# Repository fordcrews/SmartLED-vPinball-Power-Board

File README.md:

# SmartLED & Pinball Power Board v1

## Overview
SmartLED v1 is a modular, ATX-powered breakout board designed for ESP32-based lighting, solenoid, and accessory control projects such as:

- Virtual Pinball Machines  
- Holiday Light Shows  
- Aquarium Automation  
- Home Decor Lighting Systems

## Features

### 🔌 ATX/Mini-ITX Power Supply Input
- Standard 24-pin ATX connector
- `PS_ON#` control via MOSFET (GPIO or jumper selectable)
- Uses `+5VSB` to power ESP32 independently of main rails

### 🧠 ESP32 DevKitC Integration
- Supports 30-pin DevKitC boards
- Powered by +5VSB with onboard regulation
- Breakout header for unused GPIOs

### 💡 Buffered LED Outputs (8x)
- 3-pin JST outputs with:
  - AHCT125 level shifters (3.3V to 5V)
  - Selectable 5V or 12V via jumper
  - Fused output per channel

### 🧰 Dual Terminal Access
- Breadboard header (J10) and cabinet terminal block (J11)
- Shared pinout, use either or both

### 🧩 GPIO Expansion
- I²C header (GND, VCC, SDA, SCL)
- Additional GPIOs for sensors, encoders, buttons, etc.

### 🔋 MOSFET Driver Sockets
- 2–4 TO-220 MOSFET slots (e.g. IRLZ44N)
- Gate control via GPIO or jumper
- Voltage selectable (5V/12V AUX)
- For solenoids, fans, relays, motors, etc.

### 🔌 Power Outputs
- USB-C / Micro USB 5V **outputs**
- 5V/12V Barrel jack **outputs**
- Drive external Pi, LED drivers, amps, etc.

### ⚡ Cabinet Power Switch Output
- Optional switched line to control cabinet-wide power
- Triggered via ESP32 or logic jumper

## Optional / Phase 2 Ideas
- Break-off compact section
- Raspberry Pi header (Zero/Full support)
- OLED display pinout for power/usage stats
- Software-based PSU shutdown/watchdog

## Design Goals
- One ATX cable powers your entire rig
- Clean, modular, safe wiring
- Minimalist or advanced builds supported
- Great for compact lighting builds or full-featured pinball control systems

---

📁 PCB, schematic, BOM, and KiCad project files coming soon!

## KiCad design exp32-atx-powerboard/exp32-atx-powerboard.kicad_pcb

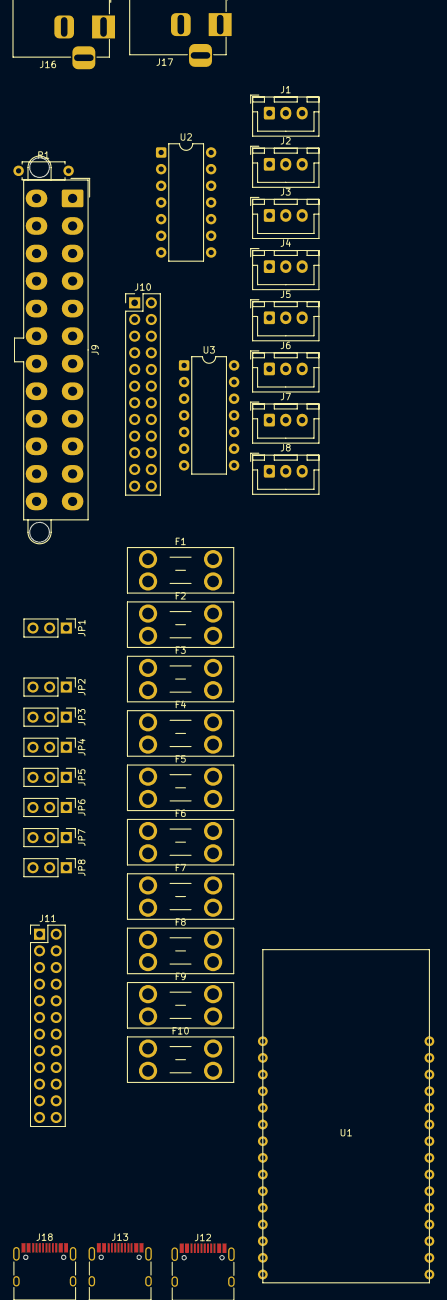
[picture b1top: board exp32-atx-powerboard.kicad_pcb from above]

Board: 2 copper layers, 38 parts (0 on the bottom side), 40 nets, no tracks yet.

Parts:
F1, F2, F3, F4, F5, F6, F7, F8, F9, F10: Fuse; Fuseholder_Blade_Mini_Keystone_3568
J1, J2, J3, J4, J5, J6, J7, J8: Conn_01x03; JST_XH_B3B-XH-A_1x03_P2.50mm_Vertical
J9: Conn_02x12_Top_Bottom; Molex_Mini-Fit_Jr_5566-24A2_2x12_P4.20mm_Vertical
J10, J11: Conn_02x12_Top_Bottom; PinHeader_2x12_P2.54mm_Vertical
J12, J13, J18: USB_C_Receptacle_PowerOnly_6P; USB_C_Receptacle_HRO_TYPE-C-31-M-12
J16, J17: Conn_01x02; BarrelJack_Horizontal
JP1, JP2, JP3, JP4, JP5, JP6, JP7, JP8: Jumper_3_Open; PinHeader_1x03_P2.54mm_Vertical
R1: 10k; R_Axial_DIN0207_L6.3mm_D2.5mm_P7.62mm_Horizontal
U1: ESP32-WROOM-32; ESP32-DevKitC_30Pin
U2, U3: 74AHCT125; DIP-14_W7.62mm

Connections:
+3.3V: J9.1, J10.1, J10.2, J10.3, J11.1, J11.2, J11.3
+5VAUX: F10.2, J10.4, J10.5, J10.6, J10.7, J10.8, J10.9, J11.4, J11.5, J11.6, J11.7, J11.8, J11.9, J12.A9 (VBUS), J12.B9 (VBUS), J18.A9 (VBUS), J18.B9 (VBUS)
+5VLED: J9.20, JP1.1 (A), JP2.1 (A), JP3.1 (A), JP4.1 (A), JP5.1 (A), JP6.1 (A), JP7.1 (A), JP8.1 (A)
+5VLOGIC: U2.14 (VCC), U3.14 (VCC)
+5V_LOGIC: J9.9, R1.1
+12VAUX: F9.1, J10.10, J10.11, J10.12, J11.10, J11.11, J11.12, J16.2, J17.2
+12VLED: J9.11, JP2.3 (B), JP3.3 (B), JP4.3 (B), JP5.3 (B), JP6.3 (B), JP7.3 (B), JP8.3 (B)
/DATA1_IN: U1.27 (IO16), U2.2
/DATA2_IN: U1.28 (IO17), U2.5
/DATA3_IN: U1.30 (IO18), U2.9
/DATA8_IN: U1.10 (IO25), U3.12
/Vout1: F1.2, J1.3
/Vout2: F2.2, J2.3
/Vout3: F3.2, J3.3
/Vout4: F4.2, J4.3
/Vout5: F5.2, J5.3
/Vout6: F6.2, J6.3
/Vout8: F8.2, J8.3
GND: J1.1, J2.1, J3.1, J4.1, J5.1, J6.1, J7.1, J8.1, J9.5, J10.13, J10.14, J10.15, J10.16, J10.17, J10.18, J10.19, J10.20, J10.21, J10.22, J10.23, J10.24, J11.13, J11.14, J11.15, J11.16, J11.17, J11.18, J11.19, J11.20, J11.21, J11.22, J11.23, J11.24, J12.A12 (GND), J12.B12 (GND), J13.A12 (GND), J13.B12 (GND), J16.1, J17.1, J18.A12 (GND), J18.B12 (GND), U2.1, U2.4, U2.7 (GND), U2.10, U2.13, U3.1, U3.4, U3.7 (GND), U3.10, U3.13
unnamed: J1.2, U2.3
unnamed: J2.2, U2.6
unnamed: J3.2, U2.8
unnamed: J4.2, U2.11
unnamed: J5.2, U3.3
unnamed: J6.2, U3.6
unnamed: J7.2, U3.8
unnamed: J8.2, U3.11
unnamed: F9.2, J9.10
unnamed: J9.16, R1.2
unnamed: F10.1, J9.21
unnamed: J13.A9 (VBUS), J13.B9 (VBUS)
unnamed: F1.1, JP1.2 (C)
unnamed: F2.1, JP2.2 (C)
unnamed: F3.1, JP3.2 (C)
unnamed: F4.1, JP4.2 (C)
unnamed: F5.1, JP5.2 (C)
unnamed: F6.1, JP6.2 (C)
unnamed: F7.1, JP7.2 (C)
unnamed: F8.1, JP8.2 (C)
unnamed: U1.1 (GND), U1.15 (GND)
